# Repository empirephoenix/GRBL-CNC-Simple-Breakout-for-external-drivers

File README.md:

# GRBL-CNC-Simple-Breakout-for-external-drivers
I wanted a simple CNC produceable breakout board, to use as a shield on, that is sufficient to be used for external motor drivers

Basically the CNC I'm running is a bit larger than the usual stock GRBL builds.

-> This means it runs with an external Brushless spindle controller, that requires the PWM signal

-> This also means that no Polulu like stepper drivers are used, instead they are external as well.

-> Last but not least, this means that space is premium in my controller box, so this shield was designed to not require more space than necessary

Additionally:

-> To allow fast building, this shield can be created with a one sided PCB, allowing it to be created with even the cheapest CNC kits

-> The amount of bridge wires is reduced as much as I'm capable of

-> Everything can either be plugged using JST (recommended) pin headers, or directly solderd onto the board

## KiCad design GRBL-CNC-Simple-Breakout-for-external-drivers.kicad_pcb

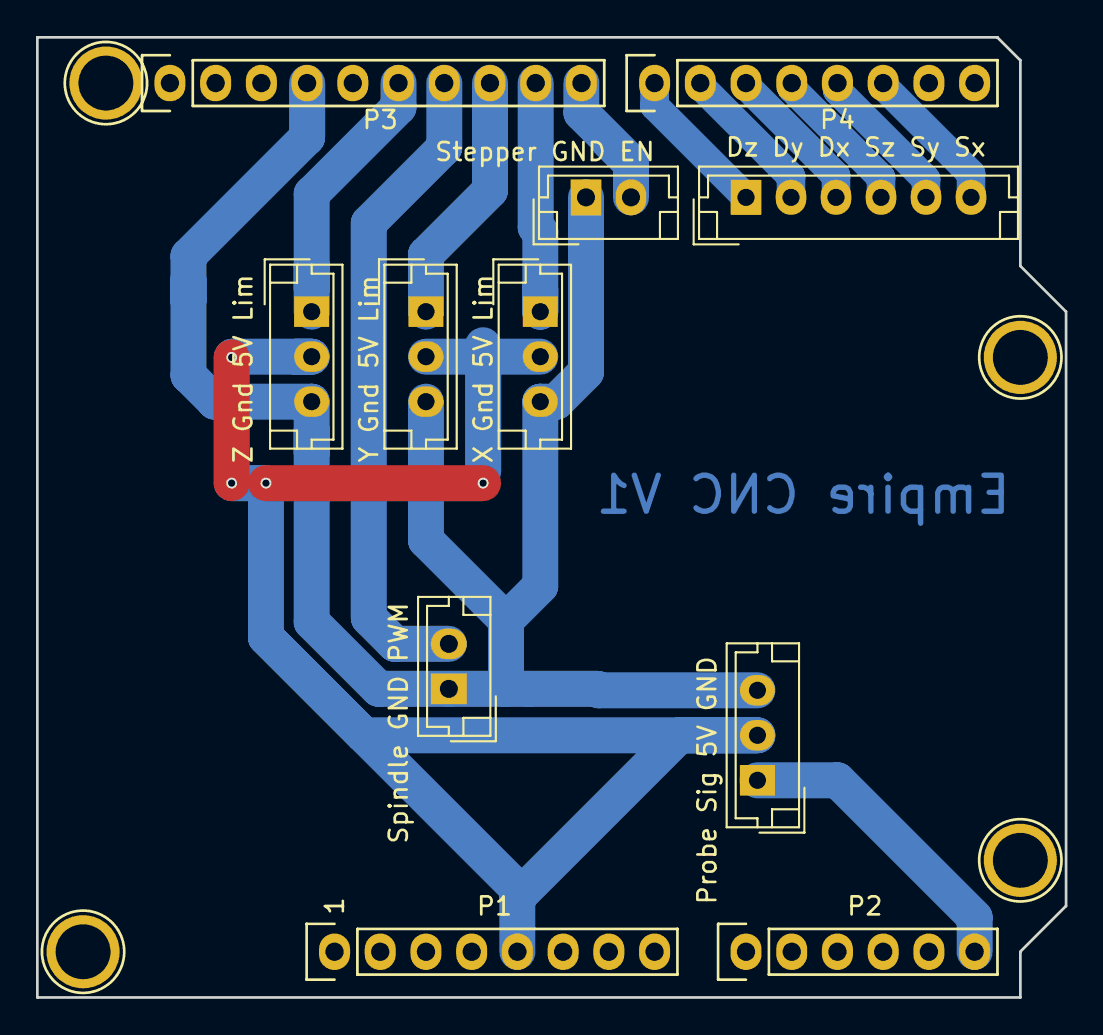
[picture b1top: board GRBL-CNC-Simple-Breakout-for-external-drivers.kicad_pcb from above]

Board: 2 copper layers, 57.2 x 53.3 mm, 15 parts (0 on the bottom side), 14 nets.

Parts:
Dz Dy Dx Sz Sy Sx: Steppers; JST_EH_B06B-EH-A_1x06_P2.50mm_Vertical
P1: Power; Socket_Strip_Arduino_1x08
P2: Analog; Socket_Strip_Arduino_1x06
P3: Digital; Socket_Strip_Arduino_1x10
P4: Digital; Socket_Strip_Arduino_1x08
P5, P6, P7, P8: CONN_01X01; Arduino_1pin
Probe Sig 5V GND: Probe; JST_EH_B03B-EH-A_1x03_P2.50mm_Vertical
Spindle GND PWM: spindle; JST_EH_B02B-EH-A_1x02_P2.50mm_Vertical
Stepper GND EN: JST_EH_B02B-EH-A_1x02_P2.50mm_Vertical
X Gnd 5V Lim: LimitX; JST_EH_B03B-EH-A_1x03_P2.50mm_Vertical
Y Gnd 5V Lim: LimitY; JST_EH_B03B-EH-A_1x03_P2.50mm_Vertical
Z Gnd 5V Lim: LimitZ; JST_EH_B03B-EH-A_1x03_P2.50mm_Vertical

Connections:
5V: P1.5, Probe Sig 5V GND.2, X Gnd 5V Lim.2, Y Gnd 5V Lim.2, Z Gnd 5V Lim.2
DirX: Dz Dy Dx Sz Sy Sx.3, P4.3
DirY: Dz Dy Dx Sz Sy Sx.2, P4.2
DirZ: Dz Dy Dx Sz Sy Sx.1, P4.1
GND-USB: P3.4, Probe Sig 5V GND.3, Spindle GND PWM.1, Stepper GND EN.1, X Gnd 5V Lim.3, Y Gnd 5V Lim.3, Z Gnd 5V Lim.3
LimitX: P3.9, X Gnd 5V Lim.1
LimitY: P3.8, Y Gnd 5V Lim.1
LimitZ: P3.6, Z Gnd 5V Lim.1
Probe: P2.6, Probe Sig 5V GND.1
SpindlePWM: P3.7, Spindle GND PWM.2
StepX: Dz Dy Dx Sz Sy Sx.6, P4.6
StepY: Dz Dy Dx Sz Sy Sx.5, P4.5
StepZ: Dz Dy Dx Sz Sy Sx.4, P4.4
StepperEN: P3.10, Stepper GND EN.2

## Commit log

2019-03-25 V1 design
2019-03-26 increased traces width, to produce it without any z homing capability (aka allow breadboard controller with minimal wireing to produce this)
